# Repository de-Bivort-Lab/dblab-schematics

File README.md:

# dblab_schematics

This is the de Bivort lab repository for custom hardware schematics and hardware representations for figure presentation.

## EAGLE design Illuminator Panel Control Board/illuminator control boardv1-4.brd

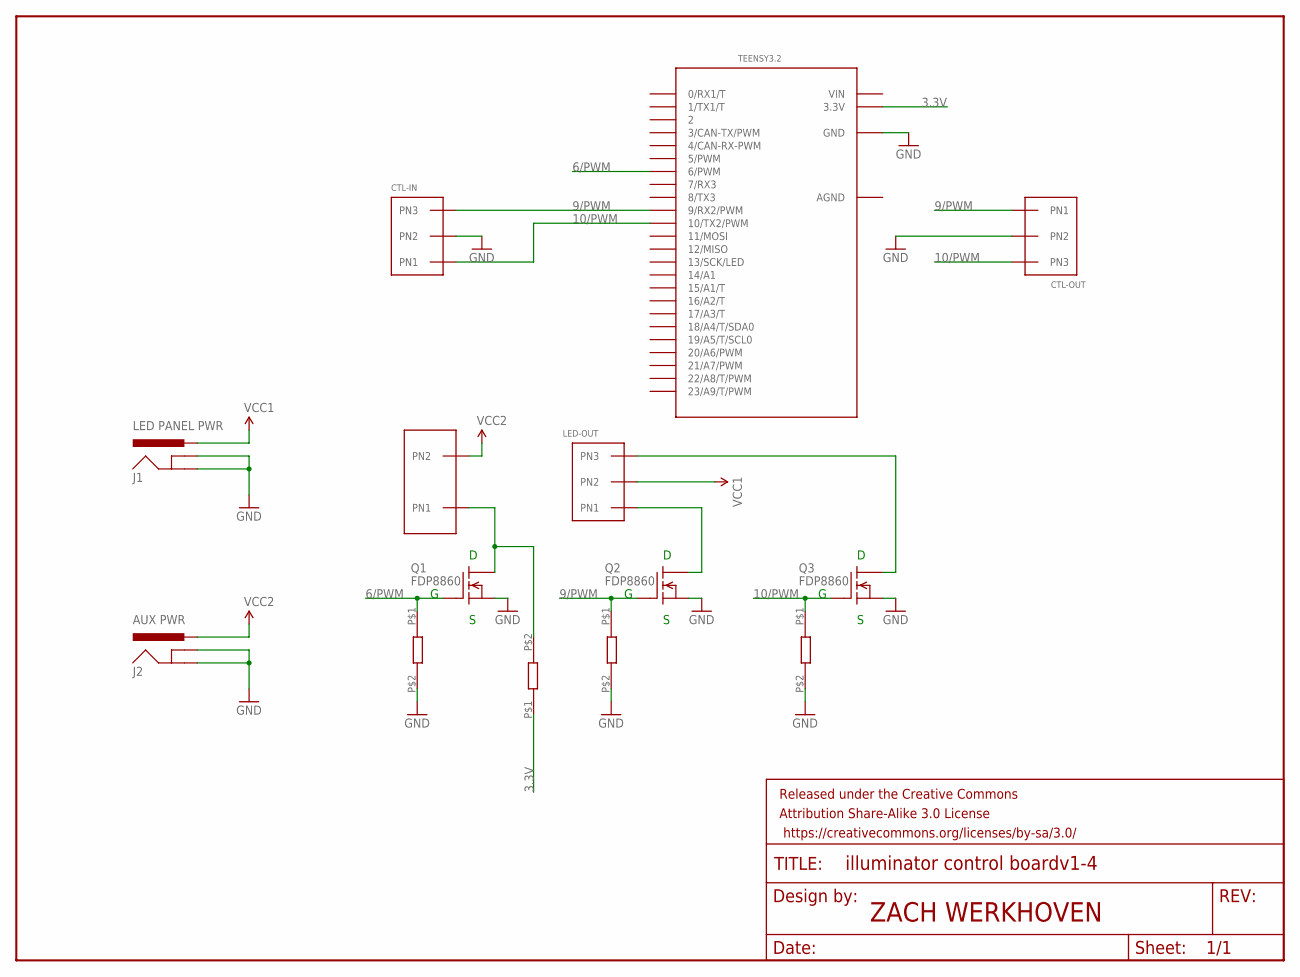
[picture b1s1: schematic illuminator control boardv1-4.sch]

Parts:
AUX-OUT: AUX-OUT; MLX-2PN
CTL-IN: MLX-3PN
CTL-OUT: MLX-3PN
FRAME1: FRAME-LETTER; CREATIVE_COMMONS
J1: LED PANEL PWR; POWER_JACK_PTH_BREAD
J2: AUX PWR; POWER_JACK_PTH_BREAD
LED-OUT: MLX-3PN
Q1, Q2, Q3: FDP8860; TO220
TEENSY3.2: TEENSY_3.1_DIL; TEENSY3-DIL
U$1, U$2, U$3, U$5: SMD-1206

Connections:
3.3V: TEENSY3.2.3.3V, U$5.P$1
6/PWM: Q1.1 (G), TEENSY3.2.6 (6/PWM), U$1.P$1
9/PWM: CTL-IN.PN3, CTL-OUT.PN1, Q2.1 (G), TEENSY3.2.9 (9/RX2/PWM), U$2.P$1
10/PWM: CTL-IN.PN1, CTL-OUT.PN3, Q3.1 (G), TEENSY3.2.10 (10/TX2/PWM), U$3.P$1
AGND: TEENSY3.2.AGND
GND: CTL-IN.PN2, CTL-OUT.PN2, J1.GND, J1.GNDBREAK, J2.GND, J2.GNDBREAK, Q1.3 (S), Q2.3 (S), Q3.3 (S), TEENSY3.2.GND, U$1.P$2, U$2.P$2, U$3.P$2
unnamed: LED-OUT.PN3, Q3.2 (D)
unnamed: LED-OUT.PN1, Q2.2 (D)
unnamed: AUX-OUT.PD1 (PN1), Q1.2 (D), U$5.P$2
VCC: AUX-OUT.PD2 (PN2), J1.PWR, J2.PWR, LED-OUT.PN2
VIN: TEENSY3.2.VIN

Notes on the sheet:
ZACH WERKHOVEN

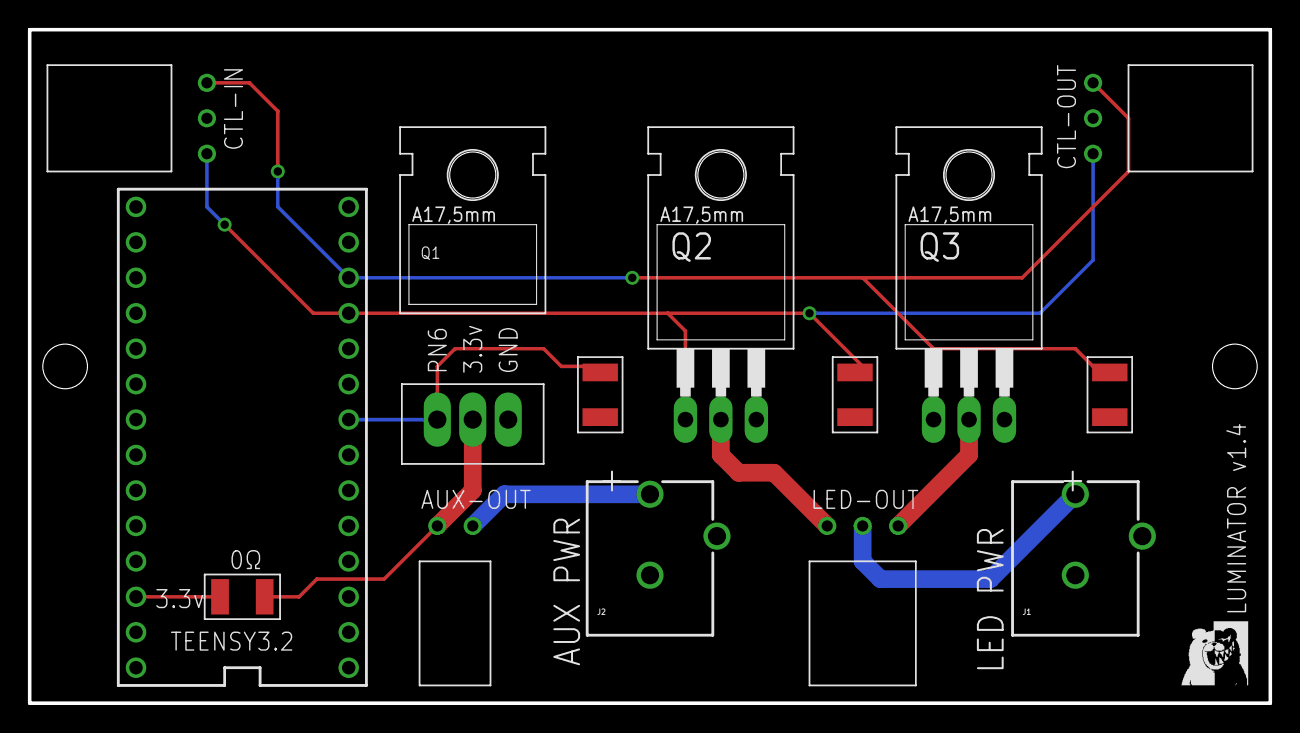
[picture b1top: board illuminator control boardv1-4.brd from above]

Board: 2 copper layers, 88.9 x 48.3 mm, 15 parts (0 on the bottom side), 9 nets.

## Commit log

2018-11-05 zach schematics - initial

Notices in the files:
parts and their libraries:
SparkFun-Connectors: Licensing: Creative Commons ShareAlike 4.0 International - https://creativecommons.org/licenses/by-sa/4.0
SparkFun-Retired: Released under the Creative Commons Attribution Share-Alike 3.0 License
SparkFun-Retired: https://creativecommons.org/licenses/by-sa/3.0
